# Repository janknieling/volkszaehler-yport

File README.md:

# volkszaehler-yport
Source files of the YPORT+ controller from Volkszähler

The original files are from https://wiki.volkszaehler.org/hardware/controllers/yport

YPORT +
=======

Hier die neue Version des YPORT-Node: der **YPORT +**

Basierend auf einem 400 MHz Atheros AR9331 SoC, in einem Modul mit 16MB Flash und 64MB DDR2 RAM,\
ermöglicht es neben USB-Host, Ethernet und WLAN, ein Debian-Derivat (OpenWRT) als Firmware zu nutzen.

Features
--------

- 1TE Hutschienengehäuse\
- Eingebautes Netzteil, Leistungsaufnahme ~ 1W (mit YPORT+_Erweiterung ~ 1,5W\
- USB-Host zum Anschluss von USB-IR-Köpfen (mehrere USB-IR-Köpfe über externen, passiven [USB-Hub](http://www.reichelt.de/LOGILINK-UA0139/3/index.html?&ACTION=3&LA=446&ARTICLE=125050&artnr=LOGILINK+UA0139&SEARCH=Logilink+Hub "http://www.reichelt.de/LOGILINK-UA0139/3/index.html?&ACTION=3&LA=446&ARTICLE=125050&artnr=LOGILINK+UA0139&SEARCH=Logilink+Hub") )\
- 10-pol. Buchsenleiste für YPORT+_Erweiterung.\
- 10/100 Mbit Ethernet-Schnittstelle\
- 802.11 b/g/n, 2.4 GHz, WLAN\
- Debian basierte Firmware ( [OpenWRT](https://openwrt.org/ "https://openwrt.org/") )\
- „vzlogger", als auch „ser2net" sind in der Firmware integriert\
- Update der Firmware über Webbrowser\
- Einfaches Sichern der Konfiguration über Webbrowser

Da sowohl „vzlogger", als auch ser2net„ auf dem YPORT + laufen, kann die middleware/Frontend auf einem beliebigen LAMP-System installiert werden.\
vzlogger wird auch in Verbindung mit der [YPORT+_Erweiterung](https://wiki.volkszaehler.org/hardware/controllers/yport_erweiterung "hardware:controllers:yport_erweiterung") genutzt, um die Daten von S0-Eingängen und 1Wire-Temperaturfühlern zur middleware zu übertragen.\
Die [YPORT+_Erweiterung](https://wiki.volkszaehler.org/hardware/controllers/yport_erweiterung "hardware:controllers:yport_erweiterung") besitzt neben S0-Eingängen, 1Wire-Busmaster, Schaltausgängen, eine Batterie gestützte RTC.

Konfiguration der LAN und WLAN-Einstellungen über Webbrowser.\
Einfache Konfiguration von „vzlogger", „ser2net" über SSH mittels Putty.\
Über „ser2net" kann der YPORT + auch als einfaches „Serial to Net - Interface" genutzt werden.

Firmware und Konfigurations-File
--------------------------------

Eine angepasste Firmware und/oder ein Konfigurations-File kann leicht eingespielt werden.\
Dazu per Browser auf den YPORT+ einloggen:\
User: root\
Password: admin\
Unter „System/Backup-Firmware-Update" findet man die Funktionen zum Konfigurations-Update bzw. Firmware-Update.\
Dort kann man auch seine eigene Konfiguration abspeichern.

Initial-Konfiguration:\
Diese wird zuerst eingespielt.\
[backup-openwrt-2015-11-14.tar.gz](https://wiki.volkszaehler.org/_media/hardware/controllers/backup-openwrt-2015-11-14.tar.gz "hardware:controllers:backup-openwrt-2015-11-14.tar.gz (13.2 KB)")

Aktuelle Firmware mit vzlogger, ser2net :\
[firmware-version_09_01_2016.rar](https://wiki.volkszaehler.org/_media/hardware/controllers/firmware-version_09_01_2016.rar "hardware:controllers:firmware-version_09_01_2016.rar (7.6 MB)")\
Diese Datei MUSS vorher entpackt werden.

Inbetriebnahme
--------------

Der YPORT ist auf DHCP eingestellt.\
Den YPORT an 230V anschließen. Vorsicht im Umgang mit Netzspannung !\
Dann den YPORT über ein Netzwerkkabel mit dem Router verbinden.\
Der Router muss den DHCP-Server eingeschaltet haben.\
Per Browser im Router nachschauen welche IP der YPORT per DHCP erhalten hat.\
Per Browser auf diese IP gehen.\
Es kommt ein Fenster zum Einloggen.\
User: root\
Passwort: admin\
Für SSH ein Passwort vergeben, z.B.: „admin"\
Abspeichern und Absenden nicht vergessen.\
Auf „Netzwerk" klicken.\
Dort auf „Drahtlos" klicken.\
Dann auf „Scan" klicken. Ein vorhandenes WLAN-Netzwerk sollte erkannt werden.\
Dann „Netzwerk beitreten" klicken.\
Dann „WPA-Schlüssel" eingeben.\
Dann die „Firewall-Zone zuweisen" : Auf „LAN" markieren.\
Dann „Absenden" klicken.\
Damit ist der YPORT sowohl per LAN, als auch per WLAN zu erreichen.\
Ggf. unter „Netzwerk"/ „Schnittstellenübersicht" bei WWAN auf „verbinden" klicken.\
Nach ein paar Sekunden wird die zugewiesene WLAN-IP angezeigt.\
Bei irgendwelchen Änderungen immer darauf achten, dass die Änderungen abgespeichert werden.\
In der obersten Zeile im Browser findet man einen entsprechenden Hinweis.

Mit PuTTY per LAN oder WLAN mit SSH einloggen.\
Auch hier User: root, Passwort: admin\
Unter /etc findet man die Konfigurationsdateien für ser2net, vzlogger.\
Diese können mit „nano" editiert werden.\
In der /etc/rc.local können die einzelnen Programme eingetragen und damit beim booten aktiviert werden\
Nach einem „reboot" sind die Programme dann aktiv.

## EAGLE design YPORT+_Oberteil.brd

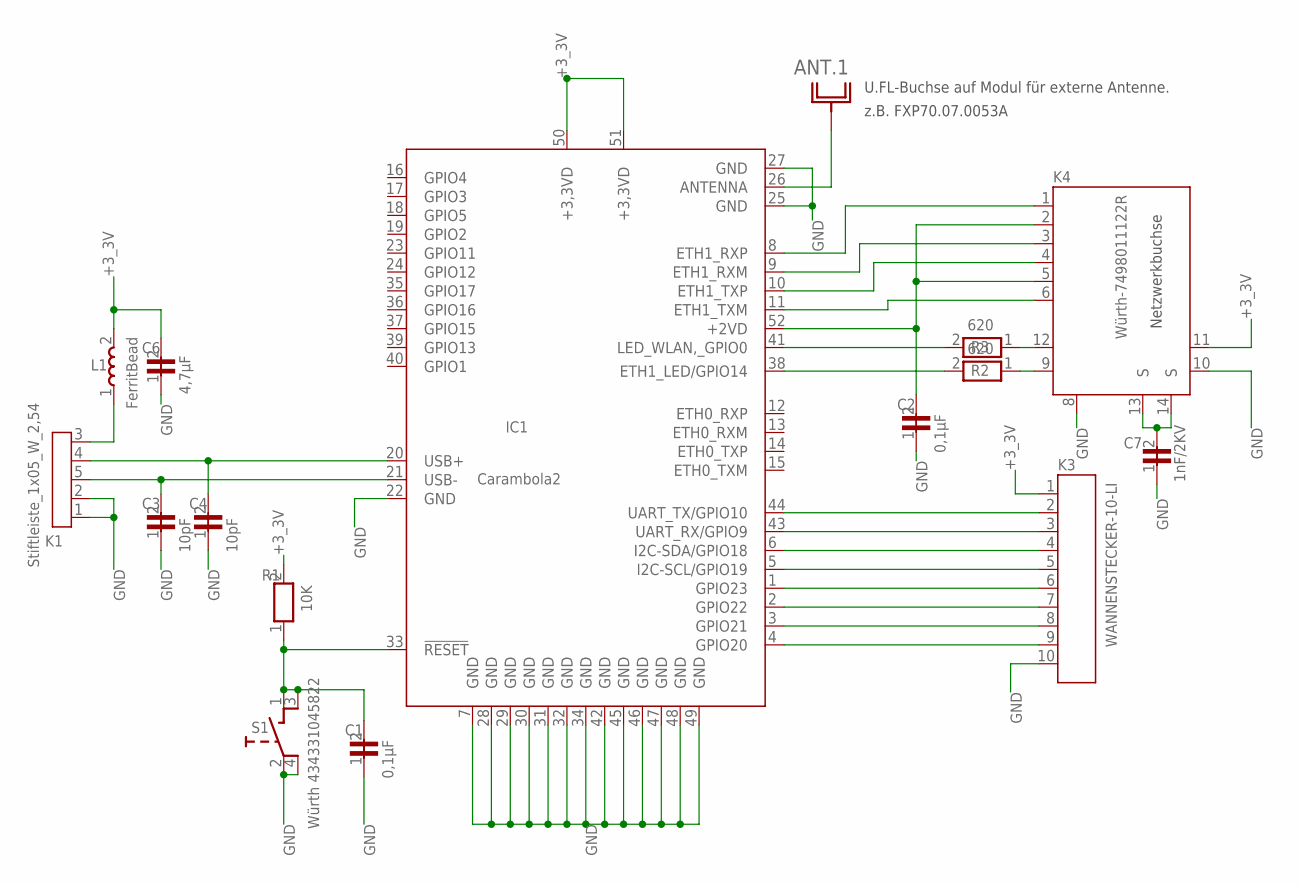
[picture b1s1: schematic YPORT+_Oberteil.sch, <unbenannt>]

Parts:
C1, C2: 0,1µF; 0603_KLEIN
C3, C4: 10pF; 0603_KLEIN
C6: 4,7µF; 0603_KLEIN
C7: 1nF/2KV; 1206
IC1: Carambola2; CARAMBOLA2
K1: Stiftleiste_1x05_W_2,54; STIFTLEISTE_1X05_G_2,54
K3: WANNENSTECKER-10-LI
K4: Würth-7498011122R; WÜRTH-7498011122R
L1: FerritBead; 0805_KLEIN
R1: 10K; 0603_KLEIN
R2, R3: 620; 0603_KLEIN
S1: Würth 434331045822; PTVF-TASTER

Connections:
1: K4.12, R3.1
2: C3.2, IC1.21 (USB-), K1.5
3: C4.2, IC1.20 (USB+), K1.4
4: K1.3, L1.1
+2VD: C2.2, IC1.52 (+2VD), K4.2, K4.5
+3_3V: C6.2, IC1.50 (+3,3VD), IC1.51 (+3,3VD), K3.1, K4.11, L1.2, R1.2
ANTENNA: IC1.26 (ANTENNA)
ETH1_RXM: IC1.9 (ETH1_RXM), K4.3
ETH1_RXP: IC1.8 (ETH1_RXP), K4.1
ETH1_TXM: IC1.11 (ETH1_TXM), K4.6
ETH1_TXP: IC1.10 (ETH1_TXP), K4.4
GND: C1.1, C2.1, C3.1, C4.1, C6.1, C7.1, IC1.7 (GND), IC1.22 (GND), IC1.25 (GND), IC1.27 (GND), IC1.28 (GND), IC1.29 (GND), IC1.30 (GND), IC1.31 (GND), IC1.32 (GND), IC1.34 (GND), IC1.42 (GND), IC1.45 (GND), IC1.46 (GND), IC1.47 (GND), IC1.48 (GND), IC1.49 (GND), K1.1, K1.2, K3.10, K4.8, K4.10, S1.2, S1.4
GPIO14: IC1.41 (LED_WLAN,_GPIO0), R3.2
GPIO20: IC1.4 (GPIO20), K3.9
GPIO21: IC1.3 (GPIO21), K3.8
GPIO22: IC1.2 (GPIO22), K3.7
GPIO23: IC1.1 (GPIO23), K3.6
I2C/GPIO19: IC1.5 (I2C-SCL/GPIO19), K3.5
SIG$5: C1.2, IC1.33 (!RESET), R1.1, S1.1, S1.3
SIG$12: IC1.38 (ETH1_LED/GPIO14), R2.2
SIG$15: IC1.6 (I2C-SDA/GPIO18), K3.4
SIG$17: C7.2, K4.13 (S), K4.14 (S)
SIG$19: K4.9, R2.1
UART_RX/GPIO9: IC1.43 (UART_RX/GPIO9), K3.3
UART_TX/GPIO10: IC1.44 (UART_TX/GPIO10), K3.2

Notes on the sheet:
U.FL-Buchse auf Modul für externe Antenne.
z.B. FXP70.07.0053A
Netzwerkbuchse

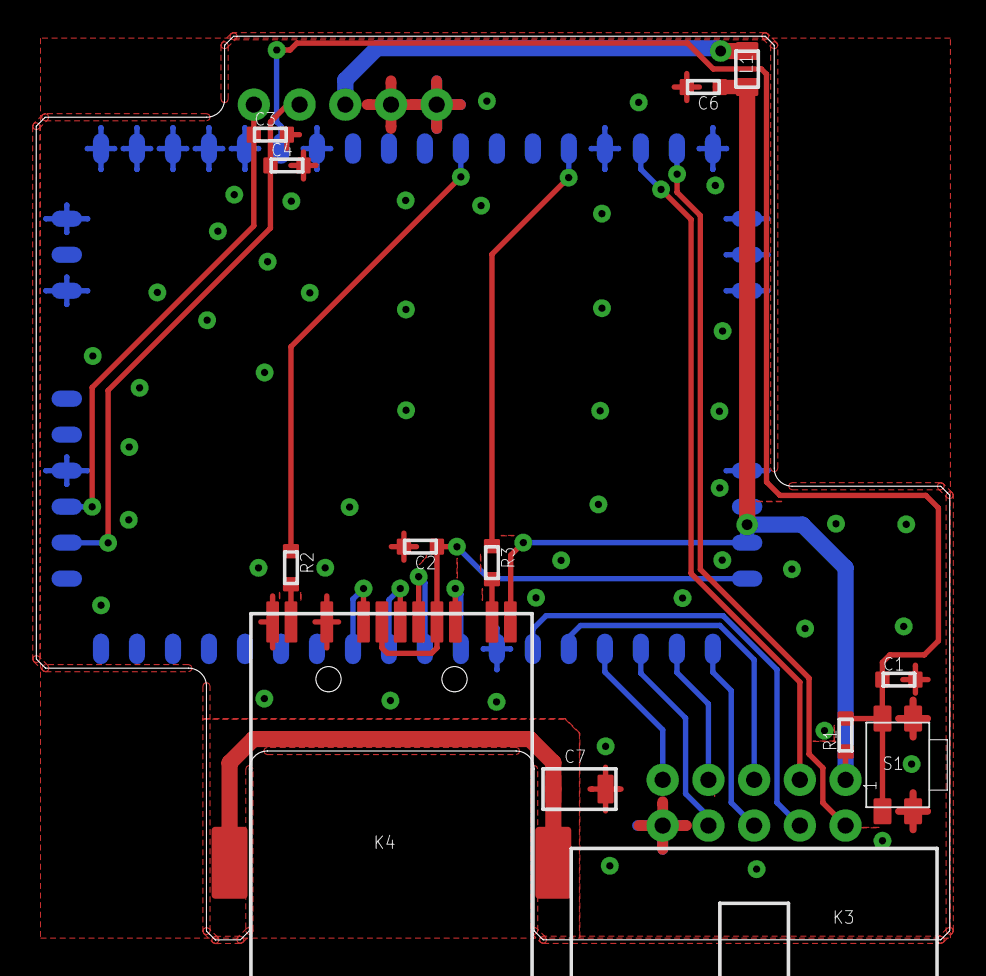
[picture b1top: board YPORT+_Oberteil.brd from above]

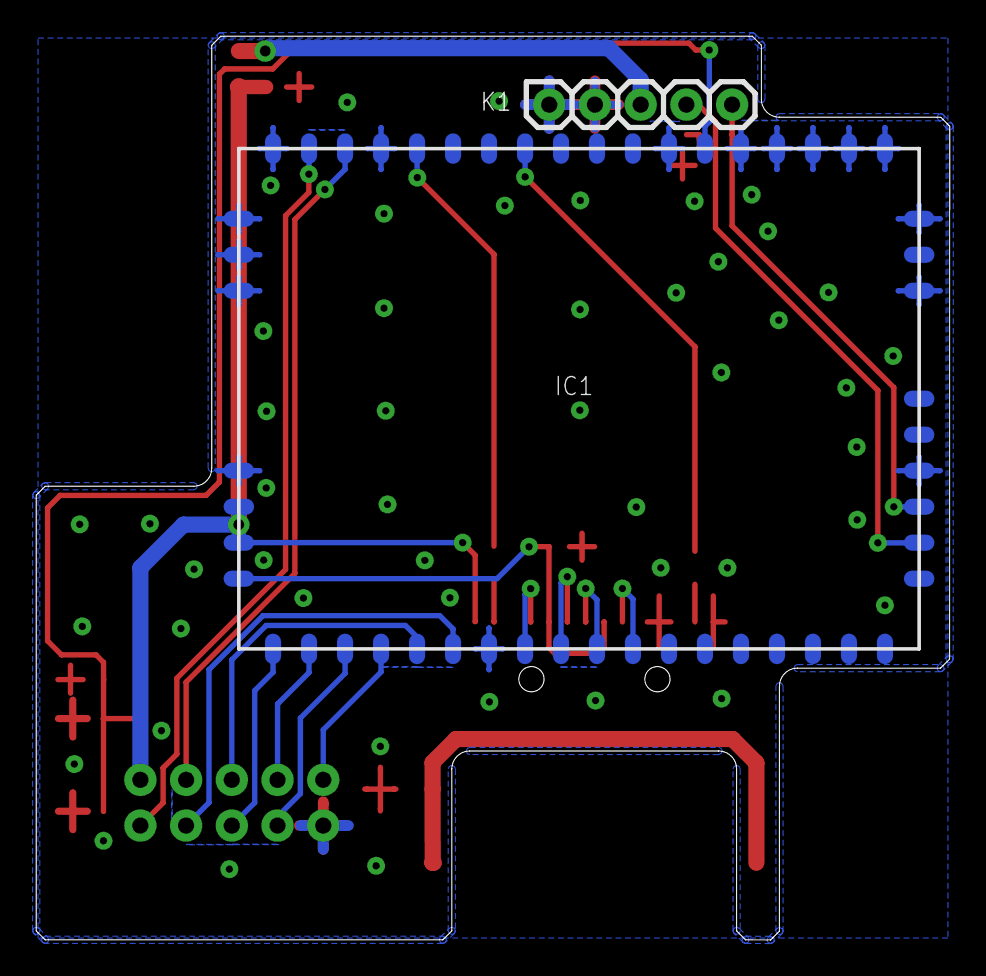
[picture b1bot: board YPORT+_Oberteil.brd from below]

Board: 2 copper layers, 50.8 x 50.2 mm, 15 parts (2 on the bottom side), 24 nets.

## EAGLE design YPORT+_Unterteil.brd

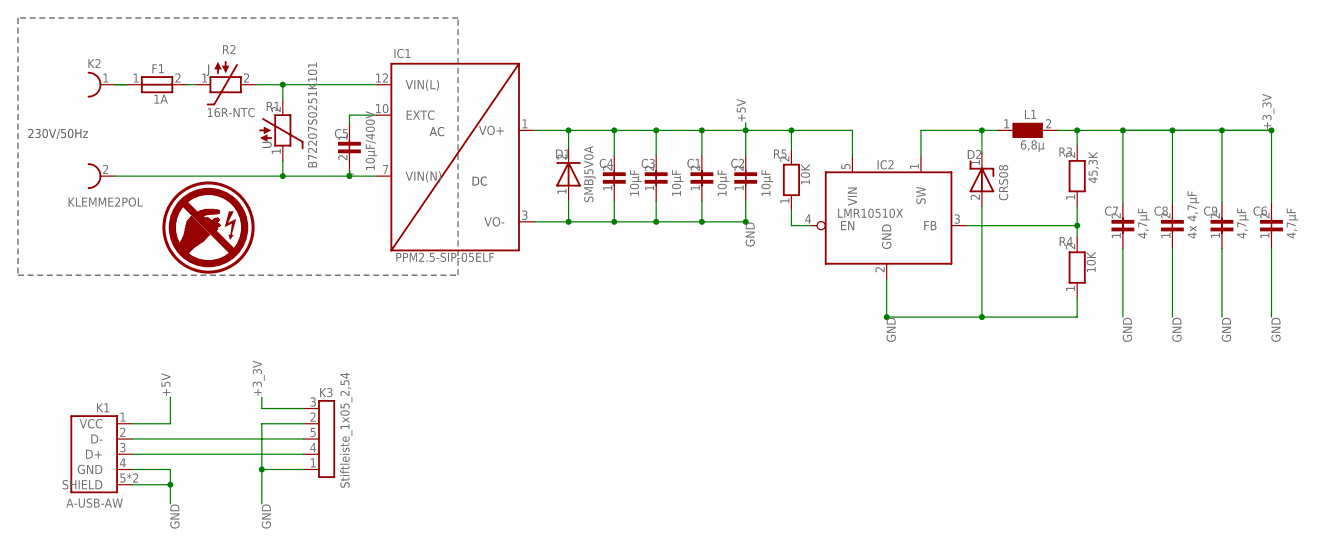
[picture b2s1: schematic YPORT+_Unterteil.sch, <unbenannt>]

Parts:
C1, C2, C3, C4: 10µF; 0805
C5: 10µF/400V; D10R5,08_ELKO
C6, C7, C9: 4,7µF; 0603_KLEIN
C8: 4x 4,7µF; 0603_KLEIN
D1: SMBJ5V0A; DO214
D2: CRS08; SOD123
F1: 1A; SMD-SICHERUNG
IC1: PPM2.5-SIP-05ELF; PPM1.65-S12-3R3ELF
IC2: LMR10510X; SOT23/5
K1: A-USB-AW; ASSMANN_A-USBS-A
K2: KLEMME2POL; AKL175_2
K3: Stiftleiste_1x05_2,54; STIFTLEISTE_1X05_G_2,54
L1: 6,8µ; WÜRTH-744025002
R1: B72207S0251K101; 6X10R5,08
R2: 16R-NTC; 6X10R5,08
R3: 45,3K; 0603_KLEIN
R4, R5: 10K; 0603_KLEIN

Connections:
+3_3V: C6.2, C7.2, C8.2, C9.2, K3.3, L1.2, R3.2
+5V: C1.2, C2.2, C3.2, C4.2, D1.2, IC1.1 (VO+), IC2.5 (VIN), K1.1 (VCC), R5.2
D+: K1.3 (D+), K3.4
D-: K1.2 (D-), K3.5
GND: C1.1, C2.1, C3.1, C4.1, C6.1, C7.1, C8.1, C9.1, D1.1, D2.2, IC1.3 (VO-), IC2.2 (GND), K1.4 (GND), K1.5 (SHIELD), K1.5_VIA_0 (SHIELD), K3.1, K3.2, R4.1
SIG$3: F1.2, R2.1
SIG$4: IC1.12 (VIN(L)), R1.2, R2.2
SIG$5: C5.2, IC1.7 (VIN(N)), K2.2, R1.1
SIG$6: F1.1, K2.1
SIG$7: IC2.3 (FB), R3.1, R4.2
SIG$8: C5.1 (+), IC1.10 (EXTC)
SIG$9: IC2.4 (EN), R5.1
SW: D2.1, IC2.1 (SW), L1.1

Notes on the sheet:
230V/50Hz

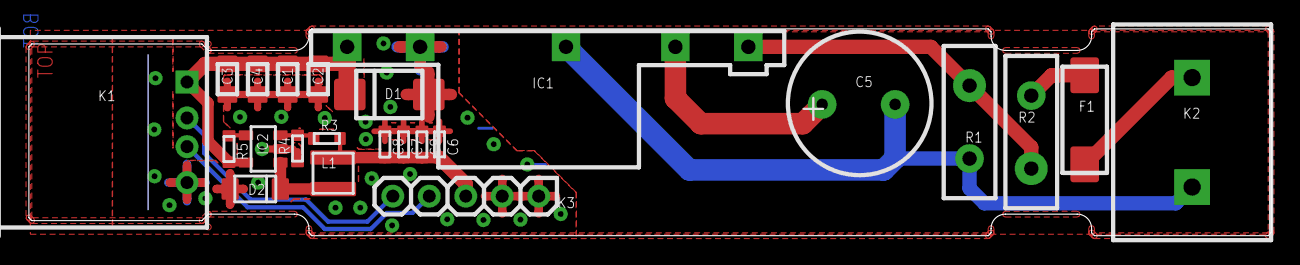
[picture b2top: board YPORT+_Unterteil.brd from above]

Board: 2 copper layers, 86.5 x 14.4 mm, 23 parts (0 on the bottom side), 13 nets.

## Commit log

2023-03-11 Initial commit; added files from Volkszaehler wiki https://wiki.volkszaehler.org/hardware/controllers/yport
2023-03-12 Converted T3001 to eagle
